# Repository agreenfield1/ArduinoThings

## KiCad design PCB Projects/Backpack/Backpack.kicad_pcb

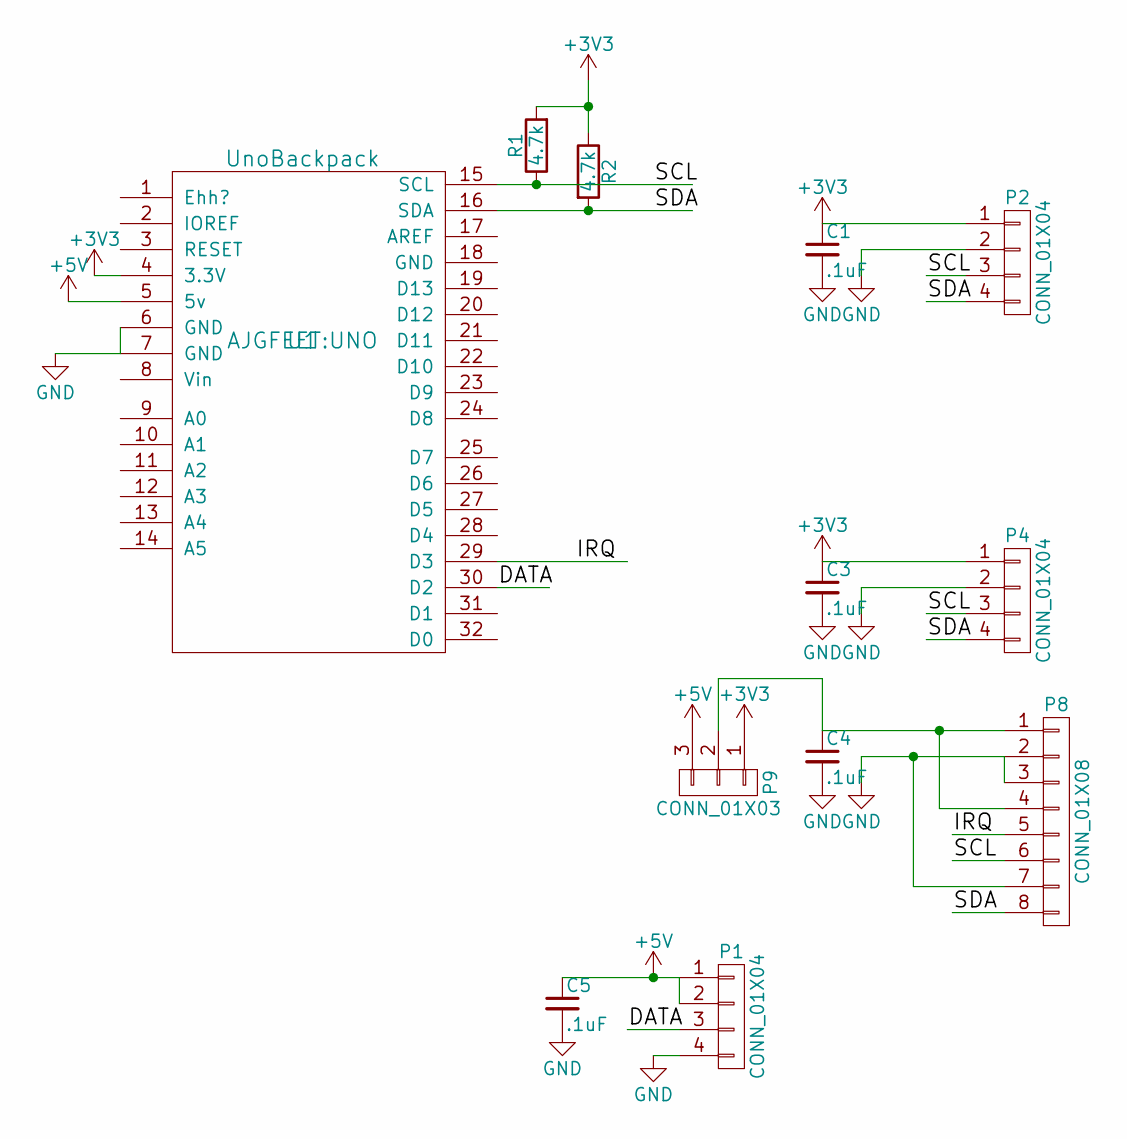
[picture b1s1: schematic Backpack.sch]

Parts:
C1, C3, C4, C5: .1uF; C_1206
P1, P2, P4: CONN_01X04; Pin_Header_Straight_1x04
P8: CONN_01X08; Pin_Header_Straight_1x08
P9: CONN_01X03; Pin_Header_Straight_1x03
R1, R2: 4.7k; R_1206
U1: UnoBackpack; UNO

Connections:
+3V3: C1.1, C3.1, P2.1, P4.1, P9.1, R1.2, R2.1, U1.4 (3.3V)
+5V: C5.1, P1.1, P1.2, P9.3, U1.5 (5v)
/DATA: P1.3, U1.30 (D2)
/IRQ: P8.5, U1.29 (D3)
/SCL: P2.3, P4.3, P8.6, R1.1, U1.15 (SCL)
/SDA: P2.4, P4.4, P8.8, R2.2, U1.16 (SDA)
GND: C1.2, C3.2, C4.2, C5.2, P1.4, P2.2, P4.2, P8.2, P8.3, P8.7, U1.6 (GND), U1.7 (GND)
unnamed: C4.1, P8.1, P8.4, P9.2

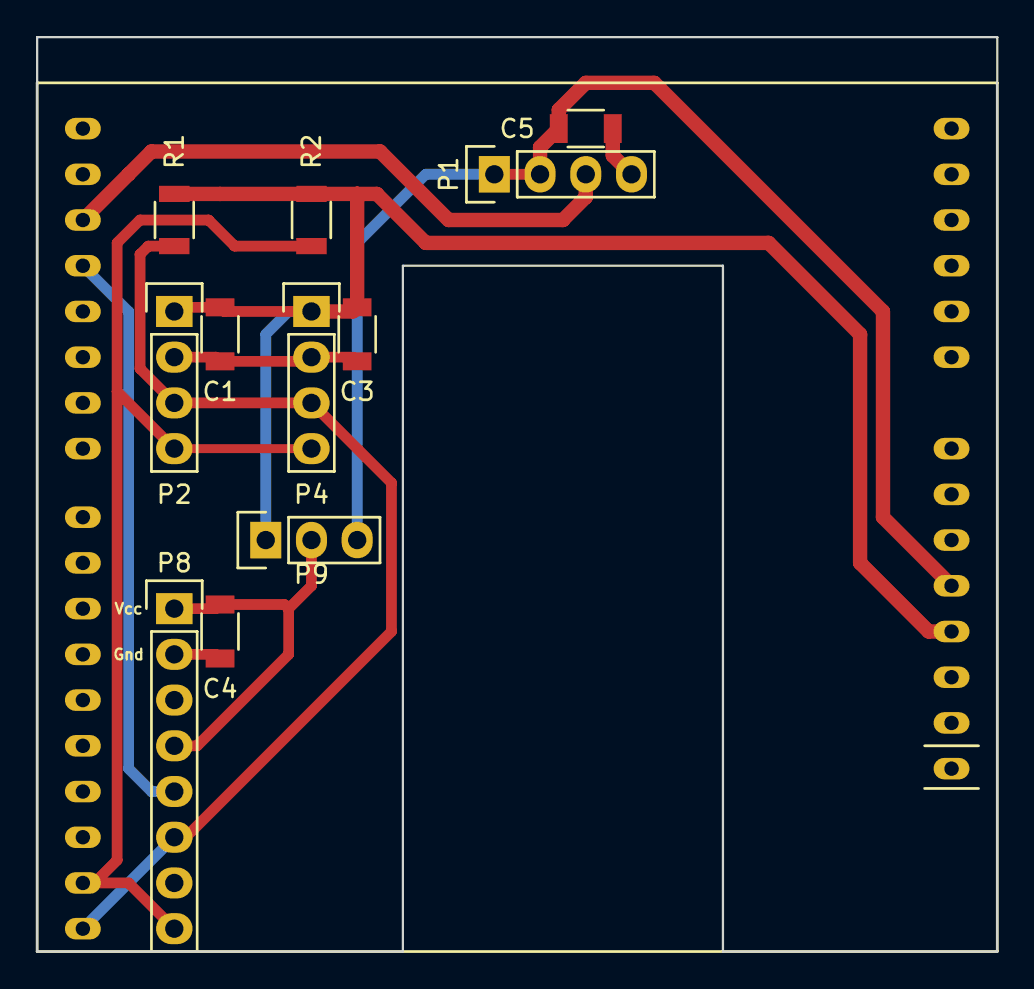
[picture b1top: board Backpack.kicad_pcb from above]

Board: 2 copper layers, 53.3 x 50.8 mm, 12 parts (0 on the bottom side), 8 nets.

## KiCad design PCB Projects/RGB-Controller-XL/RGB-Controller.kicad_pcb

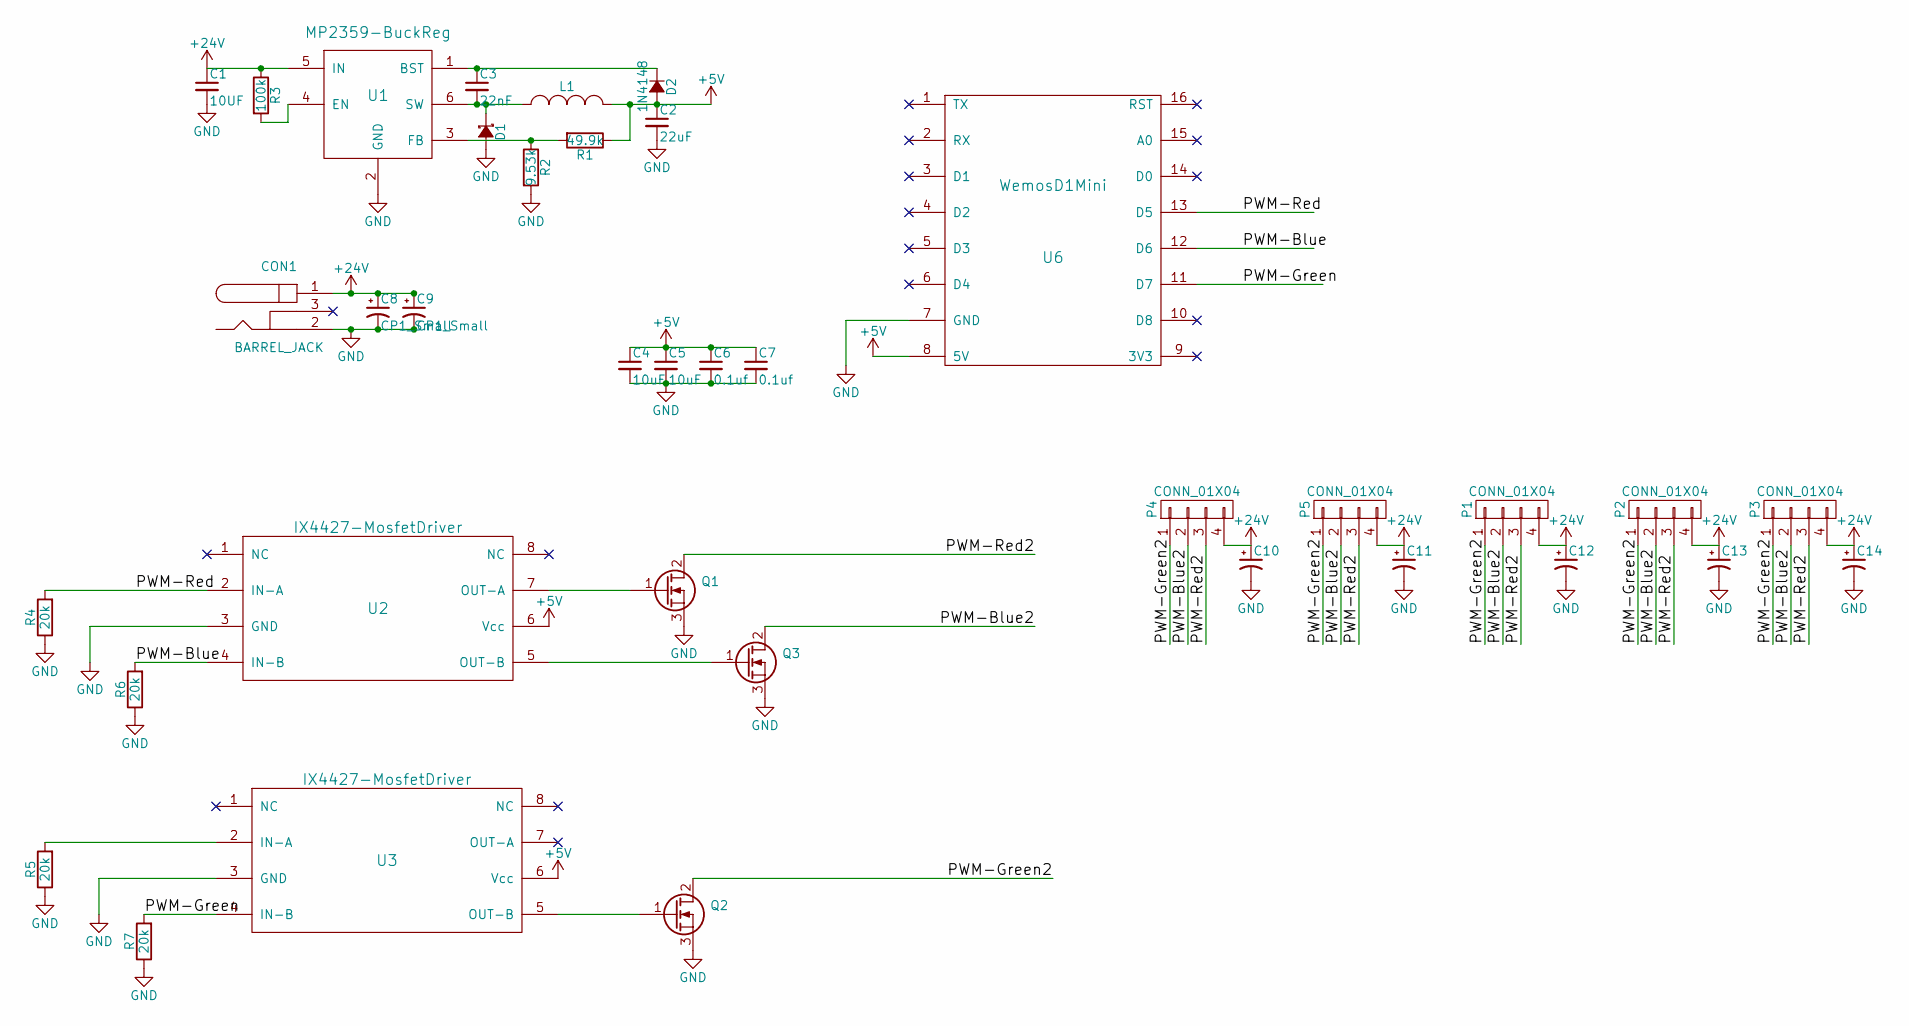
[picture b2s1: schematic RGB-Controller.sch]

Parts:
C1: 10UF; C_1206_HandSoldering
C2: 22uF; C_1206_HandSoldering
C3: 22nF; C_1206_HandSoldering
C4, C5: 10uF; C_1206_HandSoldering
C6, C7: 0.1uf; C_1206_HandSoldering
C8, C9, C10, C11, C12, C13, C14: CP1_Small; C_Radial_D10_L16_P5
CON1: BARREL_JACK; PowerPole
D1: B230A-13-F; SMA-SMB_Universal_Handsoldering
D2: 1N4148; SMB_Standard
L1: INDUCTOR_SMALL; Inductor
P1, P2, P3, P4, P5: CONN_01X04; Pin_Header_Straight_1x04
Q1, Q2, Q3: Q_NMOS_GDS; TO-220_Neutral123_Vertical
R1: 49.9k; R_1206_HandSoldering
R2: 9.53k; R_1206_HandSoldering
R3: 100k; R_1206_HandSoldering
R4, R5, R6, R7: 20k; R_1206_HandSoldering
U1: MP2359-BuckReg; SOT-23-6
U2, U3: IX4427-MosfetDriver; IX4427Feet
U6: WemosD1Mini; WemosD1MiniFeet

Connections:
+5V: C2.1, C4.1, C5.1, C6.1, C7.1, D2.2 (A), L1.2, R1.1, U2.6 (Vcc), U3.6 (Vcc), U6.8 (5V)
+24V: C1.1, C8.1, C9.1, C10.1, C11.1, C12.1, C13.1, C14.1, CON1.1, P1.4, P2.4, P3.4, P4.4, P5.4, R3.1, U1.5 (IN); also elsewhere on the board
/PWM-Blue: R6.2, U2.4 (IN-B), U6.12 (D6)
/PWM-Blue2: P1.2, P2.2, P3.2, P4.2, P5.2, Q3.2 (D)
/PWM-Green: R7.2, U3.4 (IN-B), U6.11 (D7)
/PWM-Green2: P1.1, P2.1, P3.1, P4.1, P5.1, Q2.2 (D)
/PWM-Red: R4.2, U2.2 (IN-A), U6.13 (D5)
/PWM-Red2: P1.3, P2.3, P3.3, P4.3, P5.3, Q1.2 (D)
GND: C1.2, C2.2, C4.2, C5.2, C6.2, C7.2, C8.2, C9.2, C10.2, C11.2, C12.2, C13.2, C14.2, CON1.2, D1.2 (A), Q1.3 (S), Q2.3 (S), Q3.3 (S), R2.2, R4.1, R5.1, R6.1, R7.1, U1.2 (GND), U2.3 (GND), U3.3 (GND), U6.7 (GND); also elsewhere on the board
unnamed: C3.1, D2.1 (K), U1.1 (BST)
unnamed: C3.2, D1.1 (K), L1.1, U1.6 (SW)
unnamed: Q1.1 (G), U2.7 (OUT-A)
unnamed: Q2.1 (G), U3.5 (OUT-B)
unnamed: Q3.1 (G), U2.5 (OUT-B)
unnamed: R1.2, R2.1, U1.3 (FB)
unnamed: R3.2, U1.4 (EN)
unnamed: R5.2, U3.2 (IN-A)

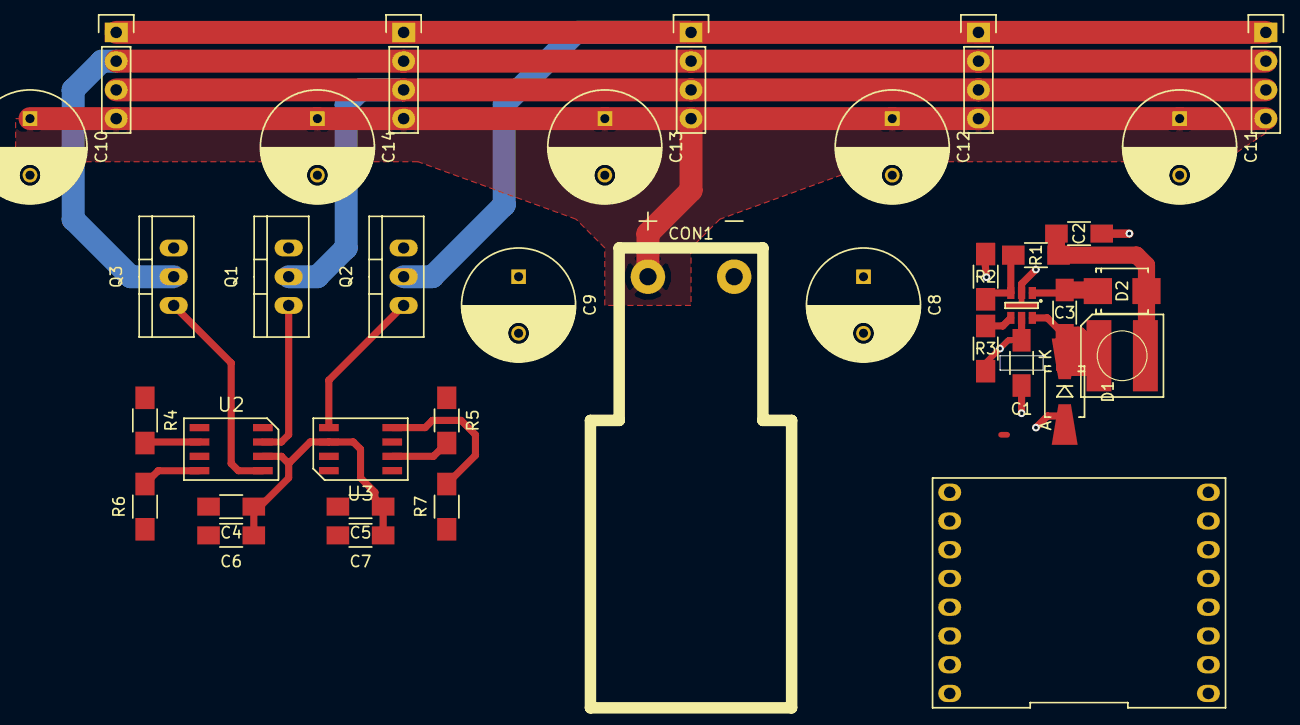
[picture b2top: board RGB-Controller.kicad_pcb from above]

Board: 2 copper layers, 38 parts (1 on the bottom side), 17 nets.

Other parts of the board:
C1#2: 10UF; C_1206_HandSoldering

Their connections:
+24V: C1#2.1; also elsewhere on the board
GND: C1#2.2; also elsewhere on the board

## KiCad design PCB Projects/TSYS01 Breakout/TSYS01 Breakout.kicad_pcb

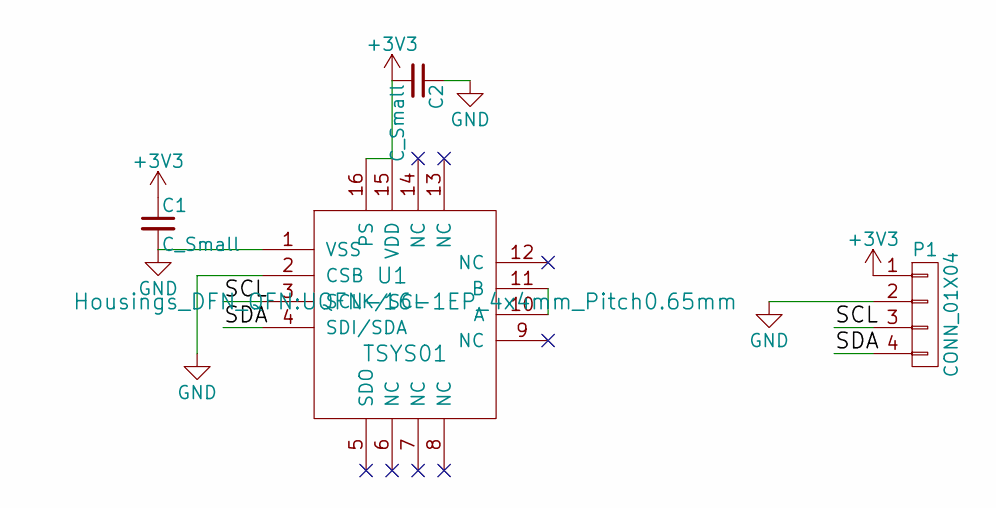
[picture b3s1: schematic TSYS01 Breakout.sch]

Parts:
C1, C2: C_Small; C_1206_HandSoldering
P1: CONN_01X04; Pin_Header_Straight_1x04
U1: TSYS01; UQFN-16-1EP_4x4mm_Pitch0.65mm

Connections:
+3V3: C1.1, C2.2, P1.1, U1.15 (VDD), U1.16 (PS)
/SCL: P1.3, U1.3 (SCLK/SCL)
/SDA: P1.4, U1.4 (SDI/SDA)
GND: C1.2, C2.1, P1.2, U1.1 (VSS), U1.2 (CSB)
unnamed: U1.10 (A), U1.11 (B)

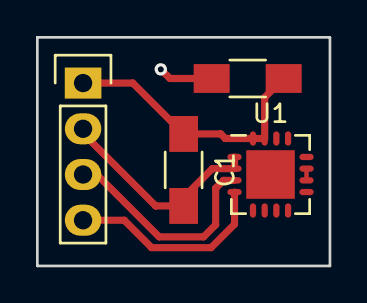
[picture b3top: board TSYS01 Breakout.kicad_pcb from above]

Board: 2 copper layers, 16.3 x 12.7 mm, 4 parts (0 on the bottom side), 5 nets.

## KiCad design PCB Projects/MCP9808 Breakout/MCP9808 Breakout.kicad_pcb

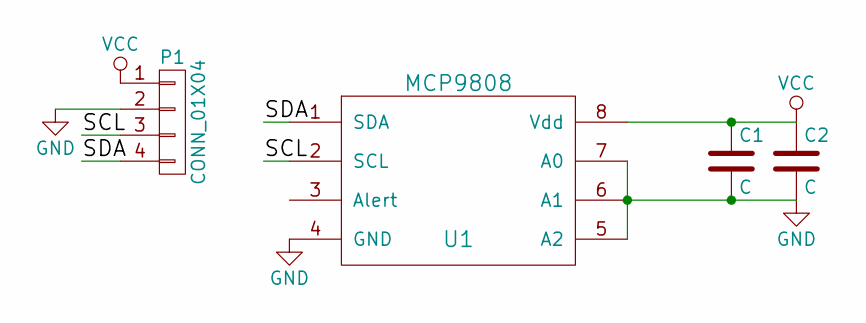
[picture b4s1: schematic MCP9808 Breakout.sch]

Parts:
C1, C2: C; C_1206_HandSoldering
P1: CONN_01X04; Pin_Header_Straight_1x04
U1: MCP9808; MSOP-8_3x3mm_Pitch0.65mm

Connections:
/SCL: P1.3, U1.2 (SCL)
/SDA: P1.4, U1.1 (SDA)
GND: C1.2, C2.2, P1.2, U1.4 (GND), U1.5 (A2), U1.6 (A1), U1.7 (A0)
VCC: C1.1, C2.1, P1.1, U1.8 (Vdd)

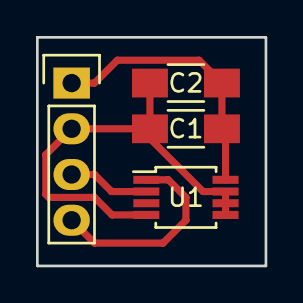
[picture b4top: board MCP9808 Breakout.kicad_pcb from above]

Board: 2 copper layers, 12.7 x 12.7 mm, 4 parts (0 on the bottom side), 4 nets.

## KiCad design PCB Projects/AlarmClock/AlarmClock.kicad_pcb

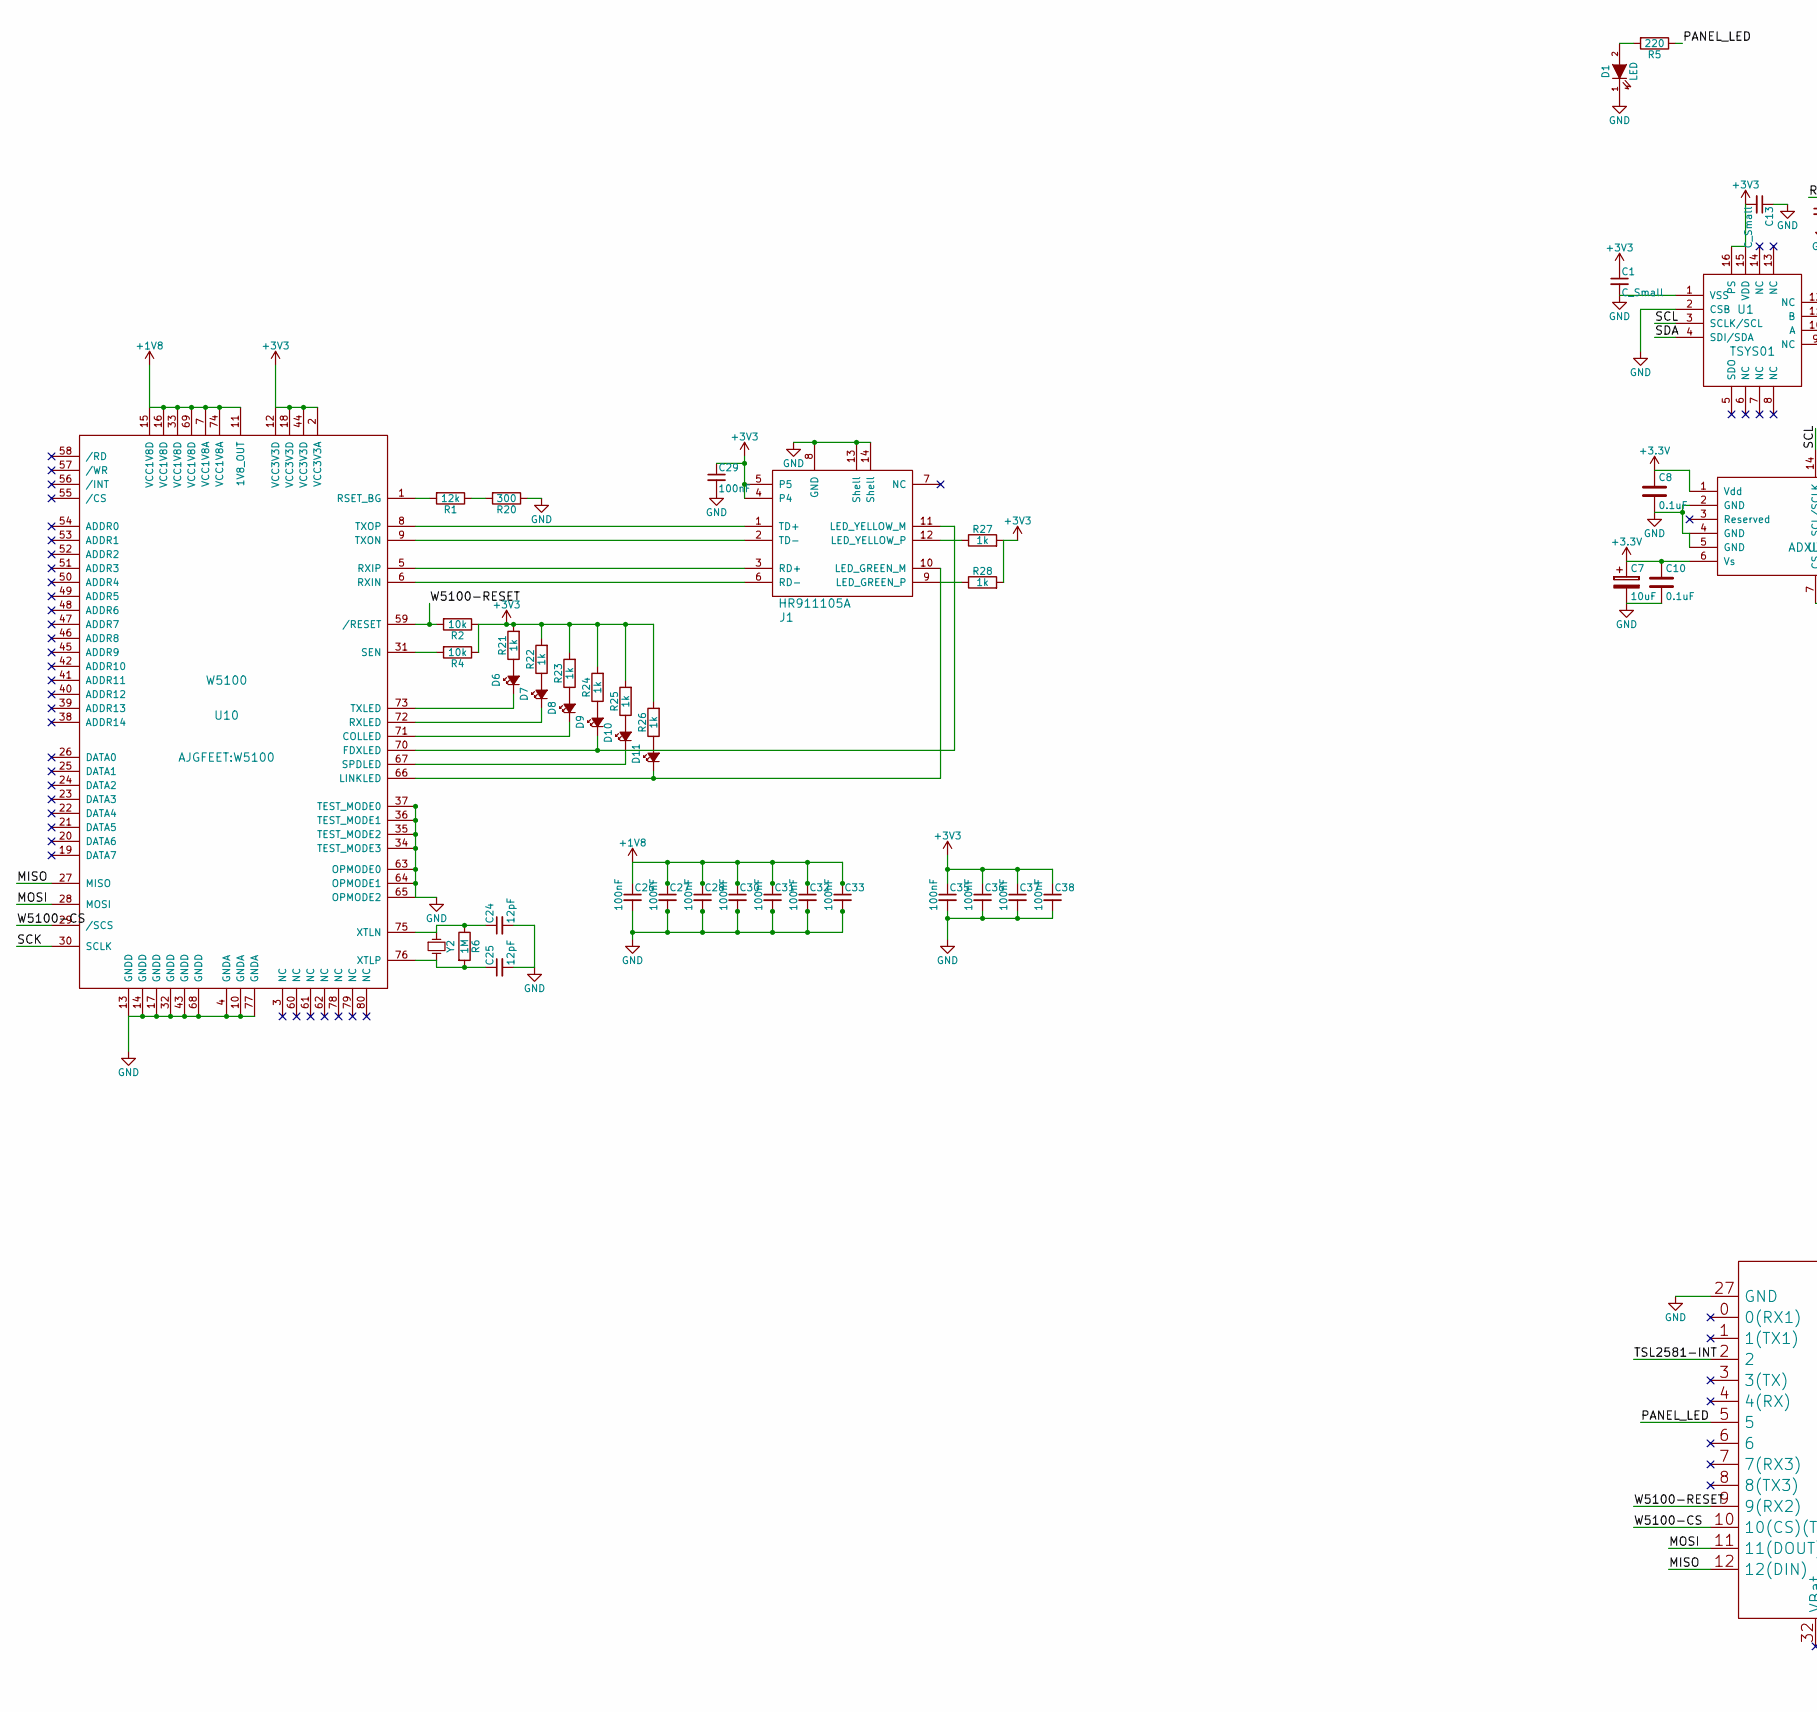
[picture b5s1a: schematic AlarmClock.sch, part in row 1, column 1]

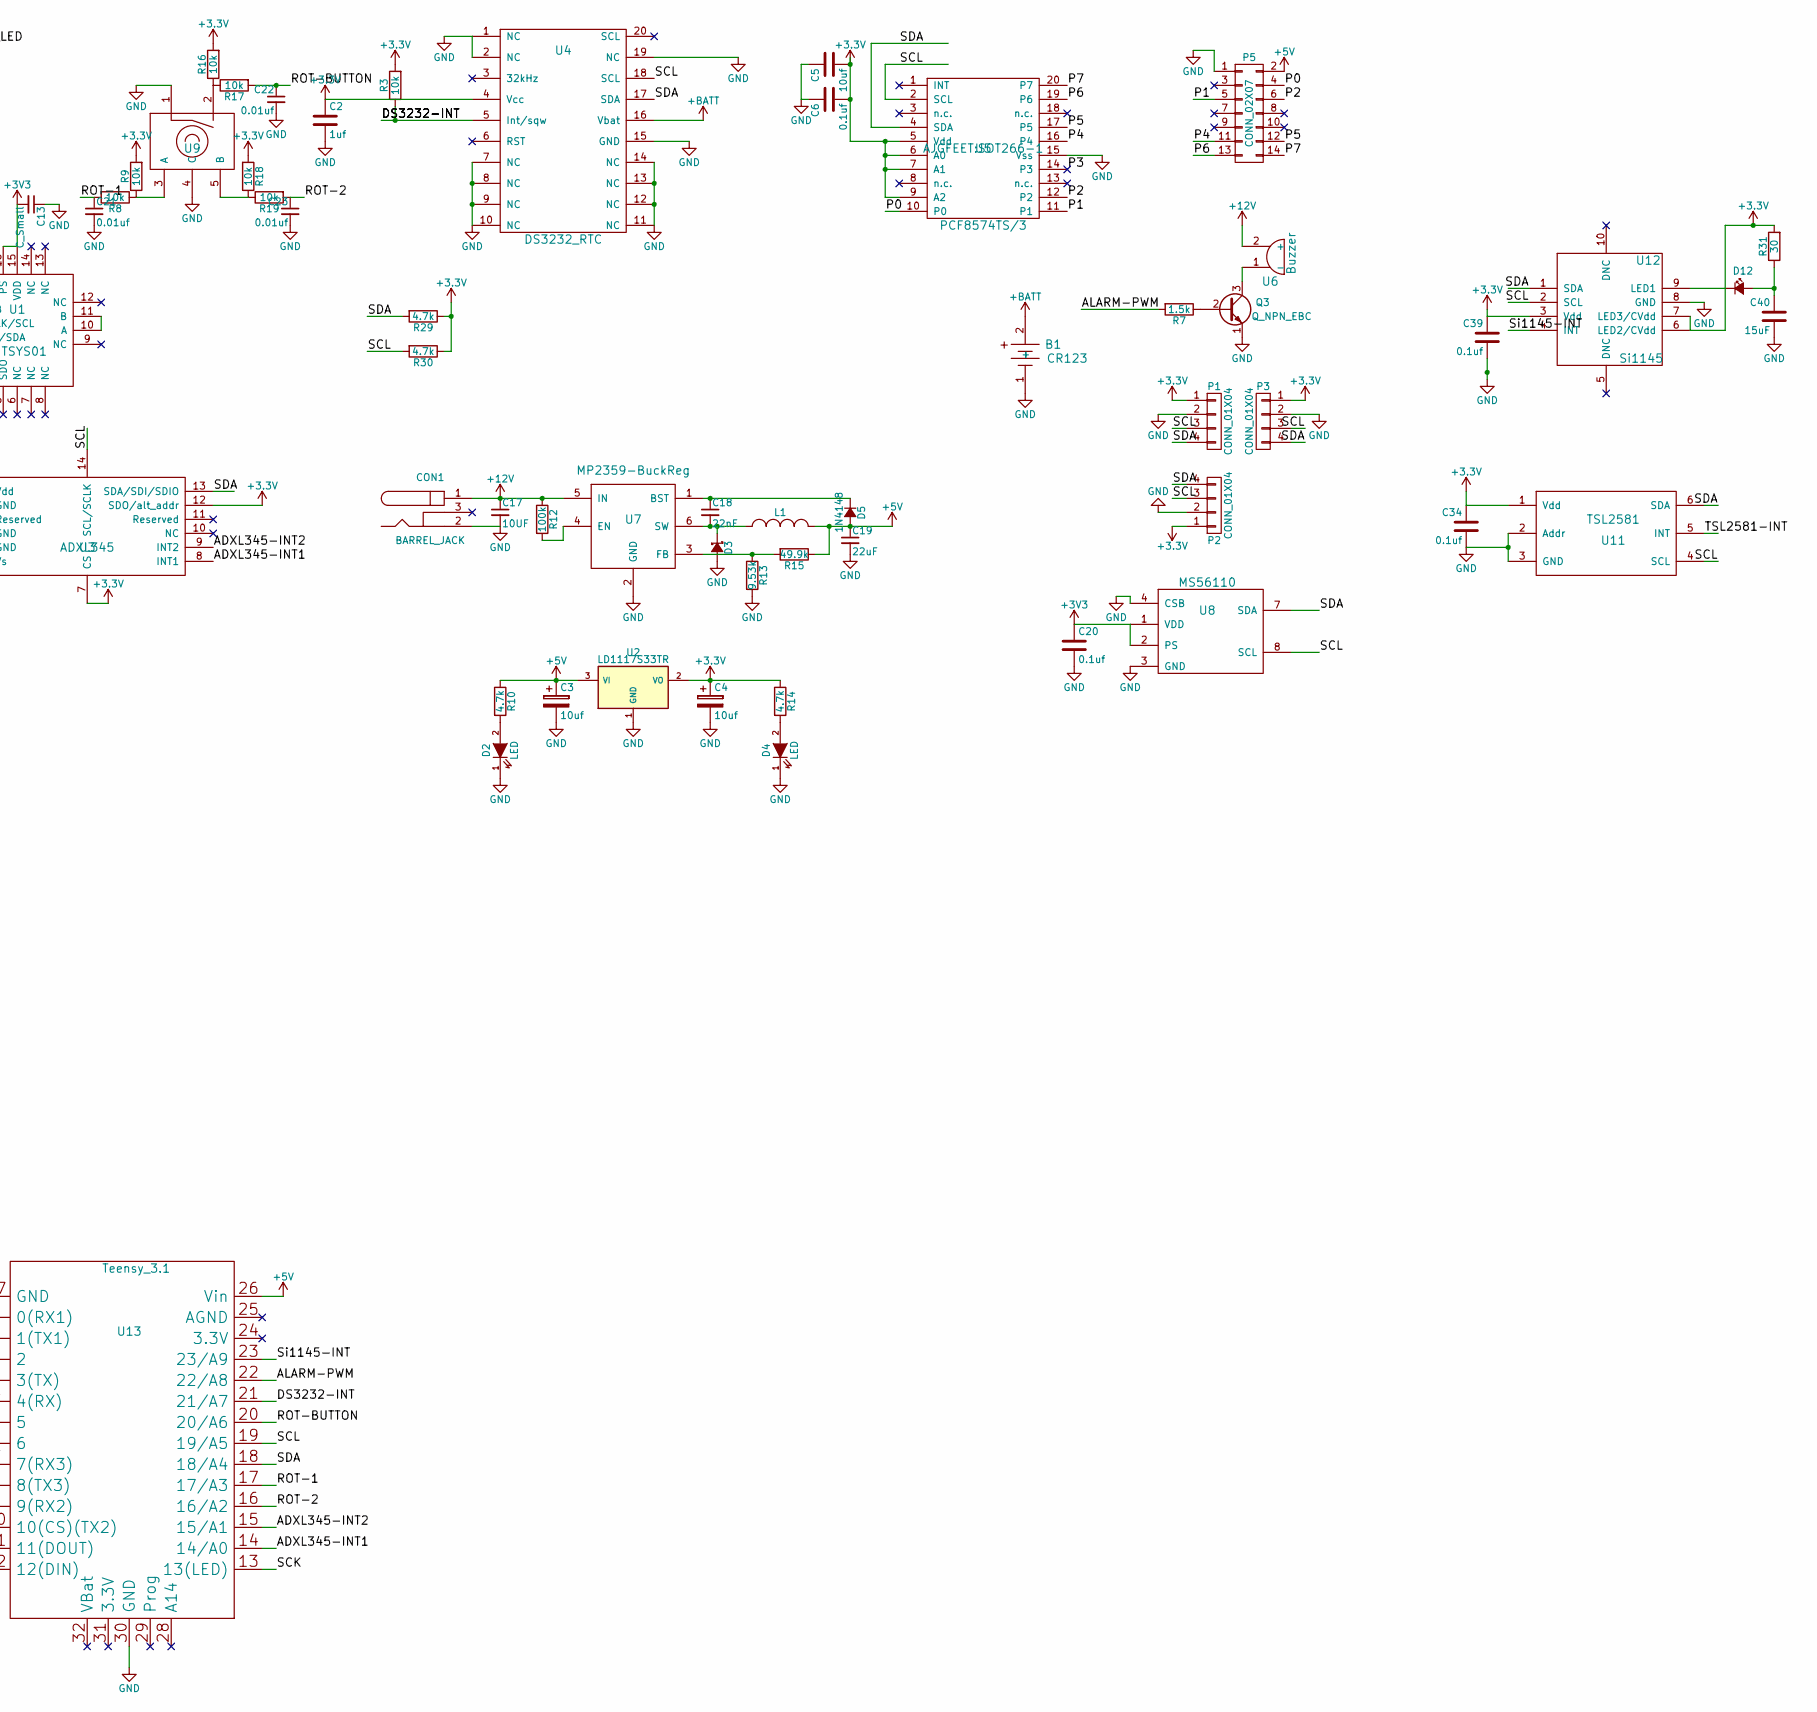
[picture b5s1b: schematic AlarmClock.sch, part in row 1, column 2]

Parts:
B1: CR123; CR2032Holder
C1, C13: C_Small; C_1206_HandSoldering
C2: 1uf; C_1206_HandSoldering
C3, C4: 10uf; SMD-1206_Pol
C5: 10uf; C_1206_HandSoldering
C6, C20, C34, C39: 0.1uf; C_1206_HandSoldering
C7: 10uF; TantalC_SizeA_EIA-3216_HandSoldering
C8, C10: 0.1uF; C_1206_HandSoldering
C17: 10UF; C_1206_HandSoldering
C18: 22nF; C_1206_HandSoldering
C19: 22uF; C_1206_HandSoldering
C21, C22, C23: 0.01uf; C_1206_HandSoldering
C24, C25: 12pF; C_1206_HandSoldering
C26, C27, C28, C29, C30, C31, C32, C33, C35, C36, C37, C38: 100nF; C_1206_HandSoldering
C40: 15uF; C_1206_HandSoldering
CON1: BARREL_JACK; JACK_ALIM
D1: LED; LED-3MM
D2, D4: LED; LED_1206
D3: B230A-13-F; SMA-SMB_Universal_Handsoldering
D5: 1N4148; Diode_DO-35_SOD27_Horizontal_RM10
D6, D7, D8, D9, D10, D11, D12: Led_Small; LED_1206
J1: HR911105A; HR911105a
L1: INDUCTOR_SMALL; Inductor
P1, P2, P3: CONN_01X04; Pin_Header_Straight_1x04
P5: CONN_02X07; Pin_Header_Straight_2x07
Q3: Q_NPN_EBC; TO-92_Rugged
R1: 12k; R_1206_HandSoldering
R2, R3, R4, R8, R9, R16, R17, R18, R19: 10k; R_1206_HandSoldering
R5: 220; R_1206_HandSoldering
R6: 1M; R_1206_HandSoldering
R7: 1.5k; R_1206_HandSoldering
R10, R14, R29, R30: 4.7k; R_1206_HandSoldering
R12: 100k; R_1206_HandSoldering
R13: 9.53k; R_1206_HandSoldering
R15: 49.9k; R_1206_HandSoldering
R20: 300; R_1206_HandSoldering
R21, R22, R23, R24, R25, R26, R27, R28: 1k; R_1206_HandSoldering
R31: 30; R_1206_HandSoldering
U1: TSYS01; UQFN-16-1EP_4x4mm_Pitch0.65mm
U2: LD1117S33TR; SOT-223
U3: ADXL345; ADXL345-ajggood
U4: DS3232_RTC; SO20(DS3232)
U5: PCF8574TS/3; SOT266-1
U6: Buzzer; Buzzer(AZ-1440S)
U7: MP2359-BuckReg; SOT-23-6
U8: MS56110; MS56110-QFN
U9: Rotary_Encoder; Pin_Header_Straight_1x05
U10: W5100
U11: TSL2581
U12: Si1145
U13: Teensy_3.1; Teensy-3.1
Y2: 25MHz; HC-18UV

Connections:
+1V8: C26.1, C27.1, C28.1, C30.1, C31.1, C32.1, C33.1, U10.7 (VCC1V8A), U10.11 (1V8_OUT), U10.15 (VCC1V8D), U10.16 (VCC1V8D), U10.33 (VCC1V8D), U10.69 (VCC1V8D), U10.74 (VCC1V8A)
+5V: C3.1, C19.1, D5.2 (A), L1.2, P5.2, R10.1, R15.1, U2.3 (VI), U13.26 (Vin)
+12V: C17.1, CON1.1, R12.1, U6.2 (+), U7.5 (IN)
+BATT: B1.2 (+), U4.16 (Vbat)
/ADXL345-INT1: U3.8 (INT1), U13.14 (14/A0)
/ADXL345-INT2: U3.9 (INT2), U13.15 (15/A1)
/ALARM-PWM: R7.2, U13.22 (22/A8)
/DS3232-INT: R3.1, U4.5 (Int/sqw), U13.21 (21/A7)
/MISO: U10.27 (MISO), U13.12 (12(DIN))
/MOSI: U10.28 (MOSI), U13.11 (11(DOUT))
/P0: P5.4, U5.10 (P0)
/P1: P5.5, U5.11 (P1)
/P2: P5.6, U5.12 (P2)
/P4: P5.11, U5.16 (P4)
/P5: P5.12, U5.17 (P5)
/P6: P5.13, U5.19 (P6)
/P7: P5.14, U5.20 (P7)
/PANEL_LED: R5.1, U13.5
/ROT-1: C21.1, R8.2, U13.17 (17/A3)
/ROT-2: C23.1, R19.2, U13.16 (16/A2)
/ROT-BUTTON: C22.1, R17.2, U13.20 (20/A6)
/SCK: U10.30 (SCLK), U13.13 (13(LED))
/SCL: P1.3, P2.3, P3.3, R30.2, U1.3 (SCLK/SCL), U3.14 (SCL/SCLK), U4.18 (SCL), U5.2 (SCL), U8.8 (SCL), U11.4 (SCL), U12.2 (SCL), U13.19 (19/A5)
/SDA: P1.4, P2.4, P3.4, R29.2, U1.4 (SDI/SDA), U3.13 (SDA/SDI/SDIO), U4.17 (SDA), U5.4 (SDA), U8.7 (SDA), U11.6 (SDA), U12.1 (SDA), U13.18 (18/A4)
/Si1145-INT: U12.4 (INT), U13.23 (23/A9)
/TSL2581-INT: U11.5 (INT), U13.2
/W5100-CS: U10.29 (/SCS), U13.10 (10(CS)(TX2))
/W5100-RESET: R2.2, U10.59 (/RESET), U13.9 (9(RX2))
GND: B1.1 (-), C1.2, C2.2, C3.2, C4.2, C5.1, C6.1, C7.2, C8.2, C10.2, C13.1, C17.2, C19.2, C20.2, C21.2, C22.2, C23.2, C24.2, C25.2, C26.2, C27.2, C28.2, C29.2, C30.2, C31.2, C32.2, C33.2, C34.2, C35.2, C36.2, C37.2, C38.2, C39.2, C40.2, CON1.2, D1.1 (K), D2.1 (K), D3.2 (A), D4.1 (K), J1.8 (GND), J1.13 (Shell), J1.14 (Shell), P1.2, P2.2, P3.2, P5.1, Q3.1 (E), R13.2, R20.1, U1.1 (VSS), U1.2 (CSB), U2.1 (GND), U3.2 (GND), U3.4 (GND), U3.5 (GND), U4.1 (NC), U4.2 (NC), U4.7 (NC), U4.8 (NC), U4.9 (NC), U4.10 (NC), U4.11 (NC), U4.12 (NC), U4.13 (NC), U4.14 (NC), U4.15 (GND), U4.19 (NC), U5.15 (Vss), U7.2 (GND), U8.3 (GND), U8.4 (CSB), U9.1, U9.4 (C), U10.4 (GNDA), U10.10 (GNDA), U10.13 (GNDD), U10.14 (GNDD), U10.17 (GNDD), U10.32 (GNDD), U10.34 (TEST_MODE3), U10.35 (TEST_MODE2), U10.36 (TEST_MODE1), U10.37 (TEST_MODE0), U10.43 (GNDD), U10.63 (OPMODE0), U10.64 (OPMODE1), U10.65 (OPMODE2), U10.68 (GNDD), U10.77 (GNDA), U11.2 (Addr), U11.3 (GND), U12.8 (GND), U13.27 (GND), U13.30 (GND)
unnamed: C18.1, D5.1 (K), U7.1 (BST)
unnamed: C18.2, D3.1 (K), L1.1, U7.6 (SW)
unnamed: C24.1, R6.1, U10.75 (XTLN), Y2.1
unnamed: C25.1, R6.2, U10.76 (XTLP), Y2.2
unnamed: C40.1, D12.2 (A), R31.1
unnamed: D1.2 (A), R5.2
unnamed: D2.2 (A), R10.2
unnamed: D4.2 (A), R14.2
unnamed: D6.1 (K), U10.73 (TXLED)
unnamed: D6.2 (A), R21.1
unnamed: D7.1 (K), U10.72 (RXLED)
unnamed: D7.2 (A), R22.1
unnamed: D8.1 (K), U10.71 (COLLED)
unnamed: D8.2 (A), R23.1
unnamed: D9.1 (K), J1.11 (LED_YELLOW_M), U10.70 (FDXLED)
unnamed: D9.2 (A), R24.1
unnamed: D10.1 (K), U10.67 (SPDLED)
unnamed: D10.2 (A), R25.1
unnamed: D11.1 (K), J1.10 (LED_GREEN_M), U10.66 (LINKLED)
unnamed: D11.2 (A), R26.1
unnamed: D12.1 (K), U12.9 (LED1)
unnamed: J1.1 (TD+), U10.8 (TXOP)
unnamed: J1.2 (TD-), U10.9 (TXON)
unnamed: J1.3 (RD+), U10.5 (RXIP)
unnamed: J1.6 (RD-), U10.6 (RXIN)
unnamed: J1.9 (LED_GREEN_P), R28.1
unnamed: J1.12 (LED_YELLOW_P), R27.1
unnamed: Q3.2 (B), R7.1
unnamed: Q3.3 (C), U6.1 (-)
unnamed: R1.1, R20.2
unnamed: R1.2, U10.1 (RSET_BG)
unnamed: R4.2, U10.31 (SEN)
unnamed: R8.1, R9.1, U9.3 (A)
unnamed: R12.2, U7.4 (EN)
unnamed: R13.1, R15.2, U7.3 (FB)
unnamed: R16.1, R17.1, U9.2
unnamed: R18.1, R19.1, U9.5 (B)
unnamed: U1.10 (A), U1.11 (B)

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
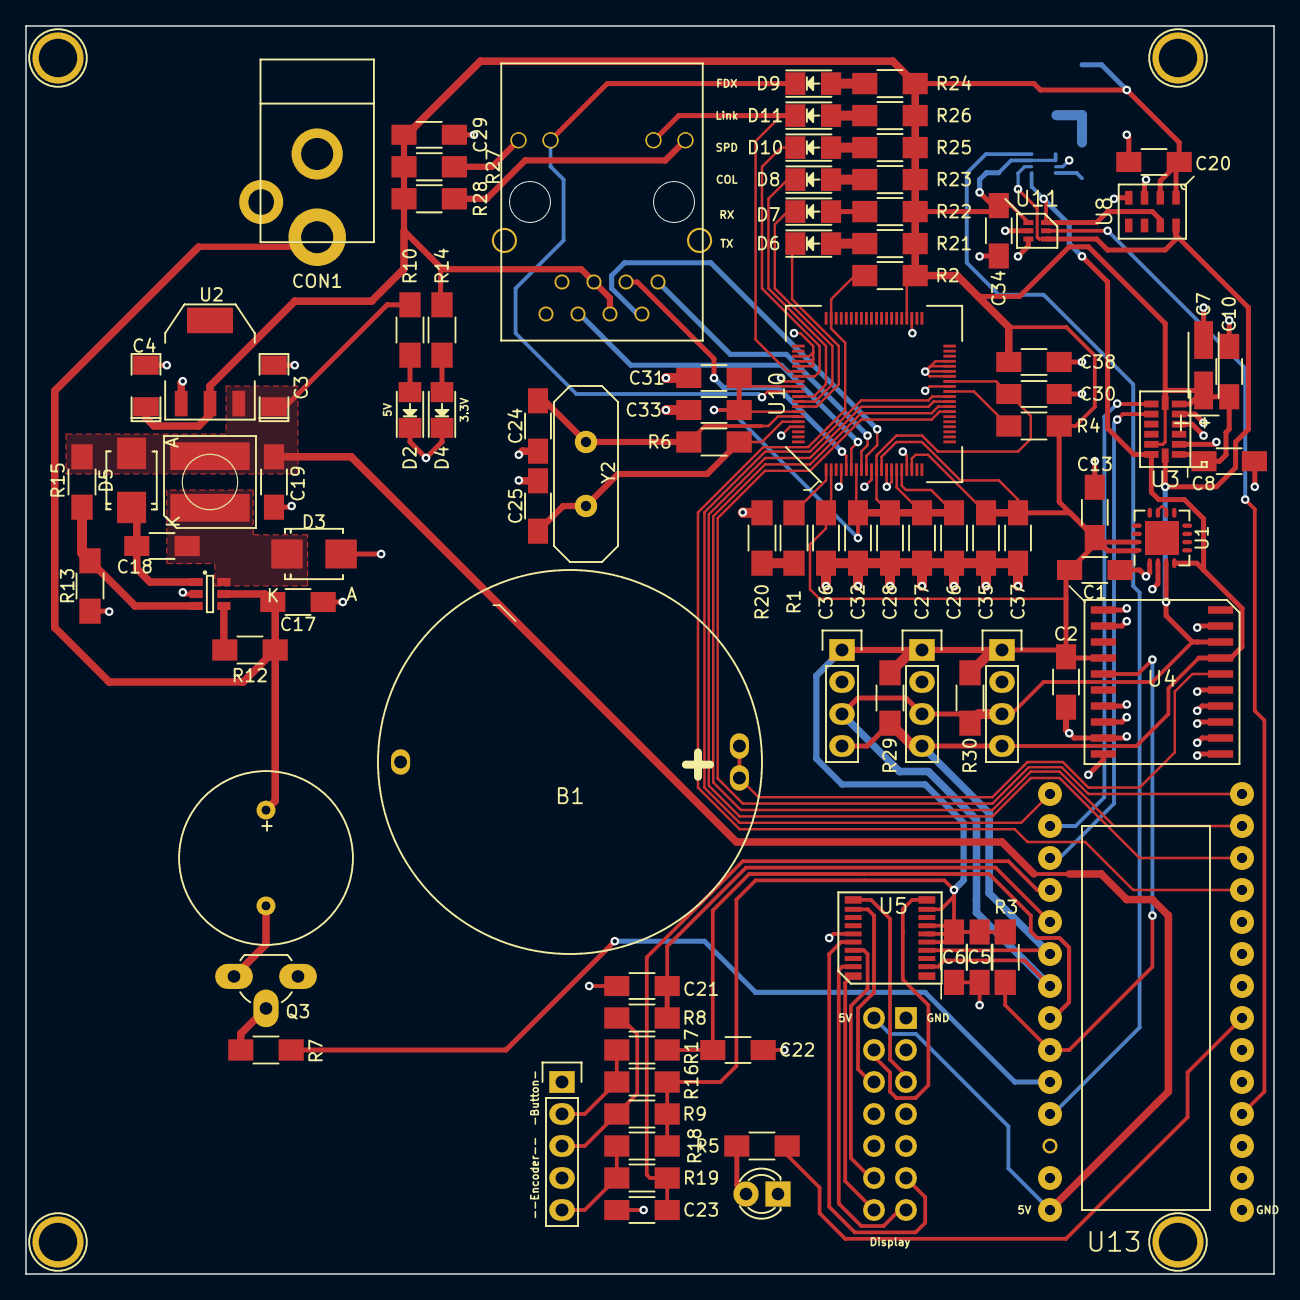
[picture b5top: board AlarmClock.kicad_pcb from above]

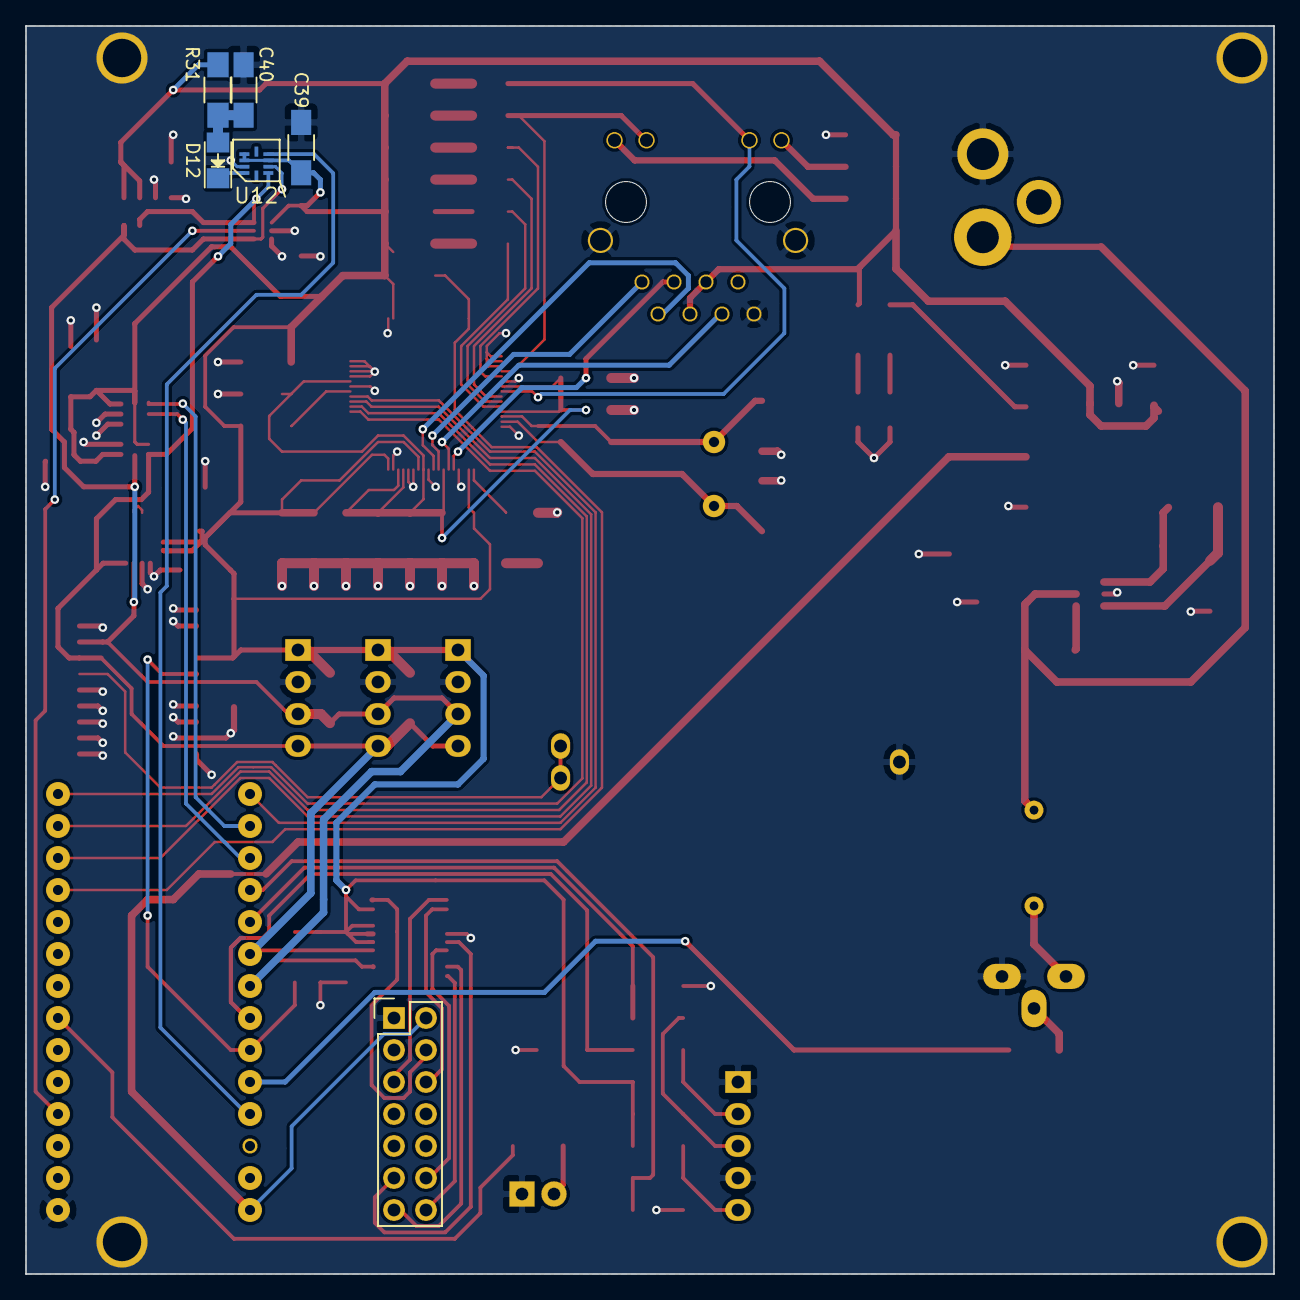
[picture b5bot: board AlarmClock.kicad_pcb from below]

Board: 2 copper layers, 99.1 x 99.1 mm, 99 parts (6 on the bottom side), 68 nets.

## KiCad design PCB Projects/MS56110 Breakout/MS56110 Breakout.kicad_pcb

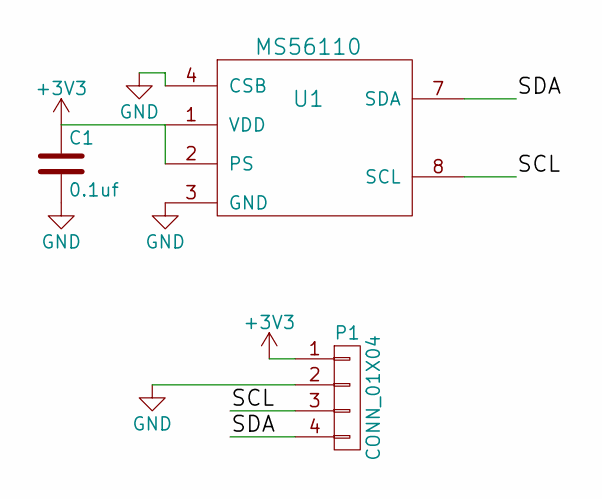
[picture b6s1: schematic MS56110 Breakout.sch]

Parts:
C1: 0.1uf; C_1206_HandSoldering
P1: CONN_01X04; Pin_Header_Straight_1x04
U1: MS56110; MS56110-QFN

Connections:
+3V3: C1.1, P1.1, U1.1 (VDD), U1.2 (PS)
/SCL: P1.3, U1.8 (SCL)
/SDA: P1.4, U1.7 (SDA)
GND: C1.2, P1.2, U1.3 (GND), U1.4 (CSB)

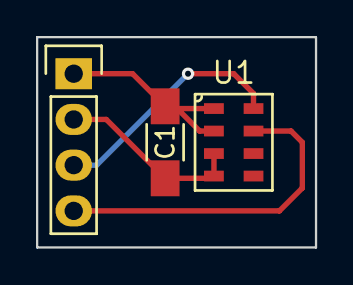
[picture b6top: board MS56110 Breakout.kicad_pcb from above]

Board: 2 copper layers, 15.5 x 11.7 mm, 3 parts (0 on the bottom side), 4 nets.
